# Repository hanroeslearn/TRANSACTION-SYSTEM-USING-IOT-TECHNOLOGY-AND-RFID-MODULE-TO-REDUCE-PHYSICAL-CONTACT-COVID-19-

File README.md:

# TRANSACTION-SYSTEM-USING-IOT-TECHNOLOGY-AND-RFID-MODULE-TO-REDUCE-PHYSICAL-CONTACT-COVID-19-
SOCIAL ASSISTANCE CASHLESS TRANSACTION SYSTEM USING IOT TECHNOLOGY TO REDUCE PHYSICAL CONTACT IN EFFORTS TO REDUCE THE IMPACT OF COVID-19  

Video: https://www.youtube.com/watch?v=onU3XBitQxs&t=15s

Made By: 
PITALOKA FORTUNA DEWI SETYORINI - Website 
HANIF IZZUDIN RAHMAN - Hardware  

Purpose: 
- Creating a cashless system for disbursement of social assistance using RFID technology 
- Create a website server to display data  

Technology: 
- Internet of Things 
- (HTTP Communication) 
- ESP-32 
- Module RFID RC522 
- LCD 16x2 + I2C 
- Database Local MySQL  

Reference: https://theiotprojects.com/connect-rf...

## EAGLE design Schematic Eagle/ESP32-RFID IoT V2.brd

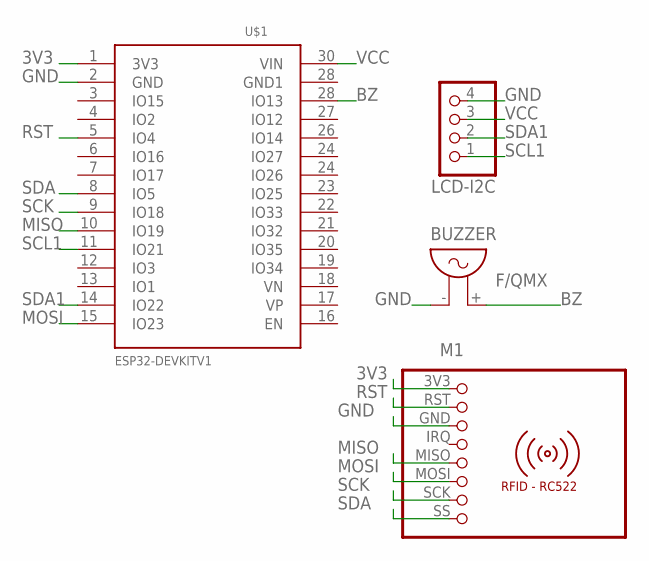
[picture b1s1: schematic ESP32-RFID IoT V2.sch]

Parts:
BUZZER: F/QMX
LCD-I2C: PINHD-1X4; 1X04
M1: RFID-RC522
U$1: ESP32DEVKITV1; ESP32-DEVKITV1

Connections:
3V3: M1.3V3 (1), U$1.1 (3V3)
BZ: BUZZER.+ (2), U$1.28 (IO13)
GND: BUZZER.- (1), LCD-I2C.4, M1.GND (3), U$1.2 (GND)
MISO: M1.MISO (5), U$1.10 (IO19)
MOSI: M1.MOSI (6), U$1.15 (IO23)
RST: M1.RST (2), U$1.5 (IO4)
SCK: M1.SCK (7), U$1.9 (IO18)
SCL1: LCD-I2C.1, U$1.11 (IO21)
SDA: M1.SS (8), U$1.8 (IO5)
SDA1: LCD-I2C.2, U$1.14 (IO22)
VCC: LCD-I2C.3, U$1.30 (VIN)

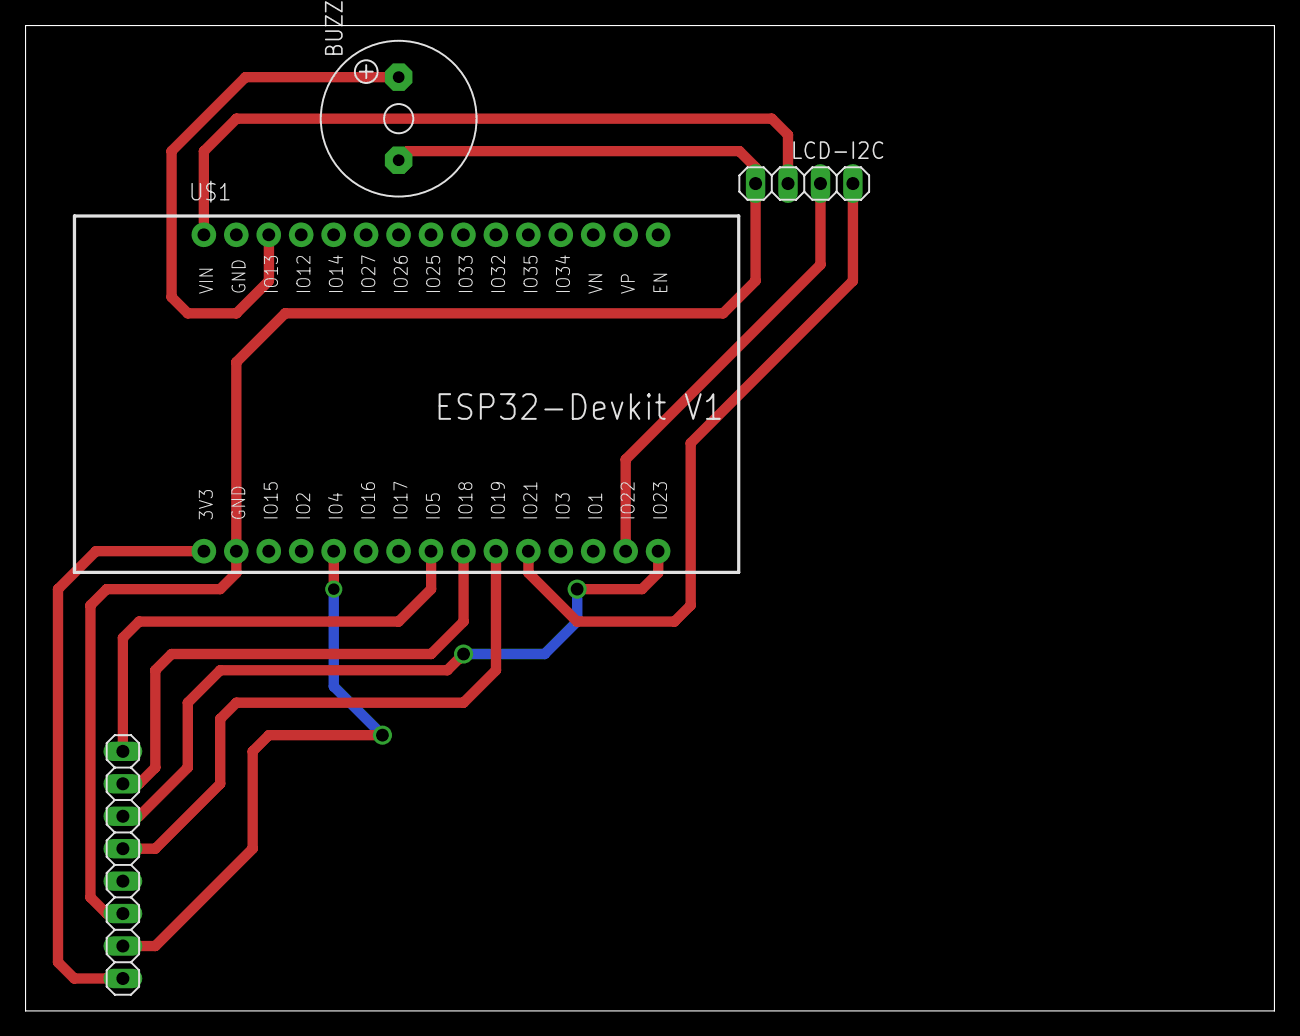
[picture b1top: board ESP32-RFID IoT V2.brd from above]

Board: 2 copper layers, 97.8 x 77.1 mm, 4 parts (0 on the bottom side), 11 nets.
